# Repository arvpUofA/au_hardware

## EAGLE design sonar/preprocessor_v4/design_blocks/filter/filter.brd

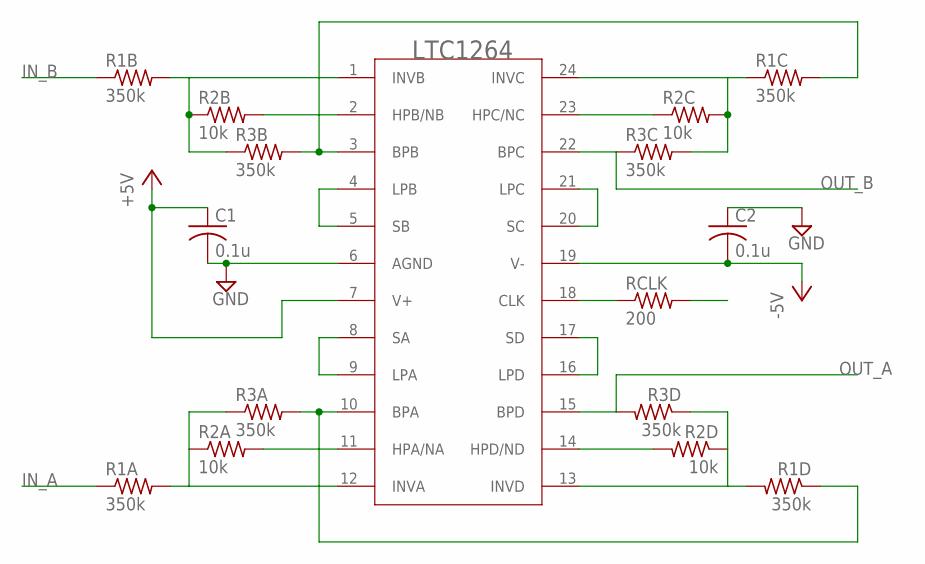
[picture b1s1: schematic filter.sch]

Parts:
C1, C2: 0.1u; C0805
R1A, R1B, R1C, R1D, R3A, R3B, R3C, R3D: 350k; R0805
R2A, R2B, R2C, R2D: 10k; R0805
RCLK: 200; R0805
U$1: LTC1264SMD; SO24W

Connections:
+5V: C1.1, U$1.7 (V+)
-5V: C2.2, U$1.19 (V-)
CLK: RCLK.2
GND: C1.2, C2.1, U$1.6 (AGND)
IN_A: R1A.1
IN_B: R1B.1
unnamed: R2D.2, U$1.14 (HPD/ND)
unnamed: R1D.2, R2D.1, R3D.1, U$1.13 (INVD)
unnamed: U$1.16 (LPD), U$1.17 (SD)
unnamed: R2C.1, U$1.23 (HPC/NC)
unnamed: R1C.1, R2C.2, R3C.2, U$1.24 (INVC)
unnamed: R2B.2, U$1.2 (HPB/NB)
unnamed: R1B.2, R2B.1, R3B.1, U$1.1 (INVB)
unnamed: U$1.4 (LPB), U$1.5 (SB)
unnamed: U$1.20 (SC), U$1.21 (LPC)
unnamed: RCLK.1, U$1.18 (CLK)
unnamed: R2A.2, U$1.11 (HPA/NA)
unnamed: U$1.8 (SA), U$1.9 (LPA)
unnamed: R1A.2, R2A.1, R3A.1, U$1.12 (INVA)
OUT_2ND_A: R1D.1, R3A.2, U$1.10 (BPA)
OUT_2ND_ORDER_B: R1C.2, R3B.2, U$1.3 (BPB)
OUT_A: R3D.2, U$1.15 (BPD)
OUT_B: R3C.1, U$1.22 (BPC)

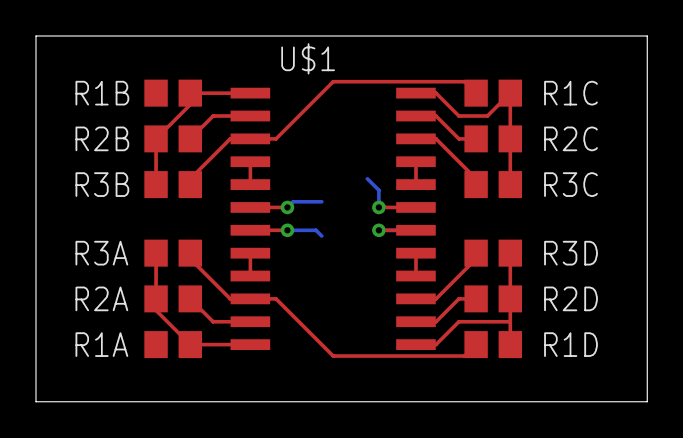
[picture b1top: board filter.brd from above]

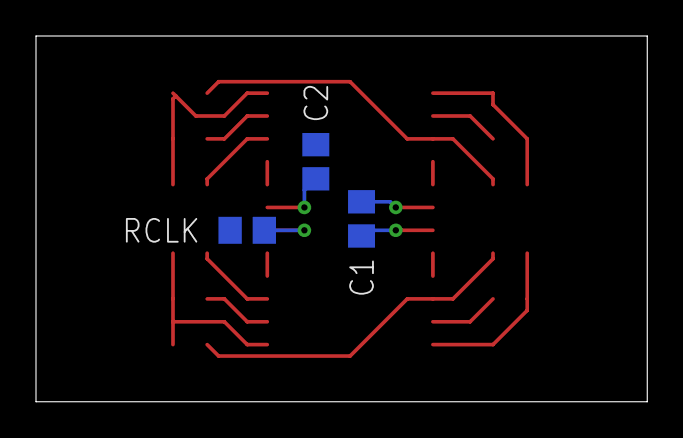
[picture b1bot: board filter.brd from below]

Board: 2 copper layers, 34.0 x 20.3 mm, 16 parts (3 on the bottom side), 20 nets.

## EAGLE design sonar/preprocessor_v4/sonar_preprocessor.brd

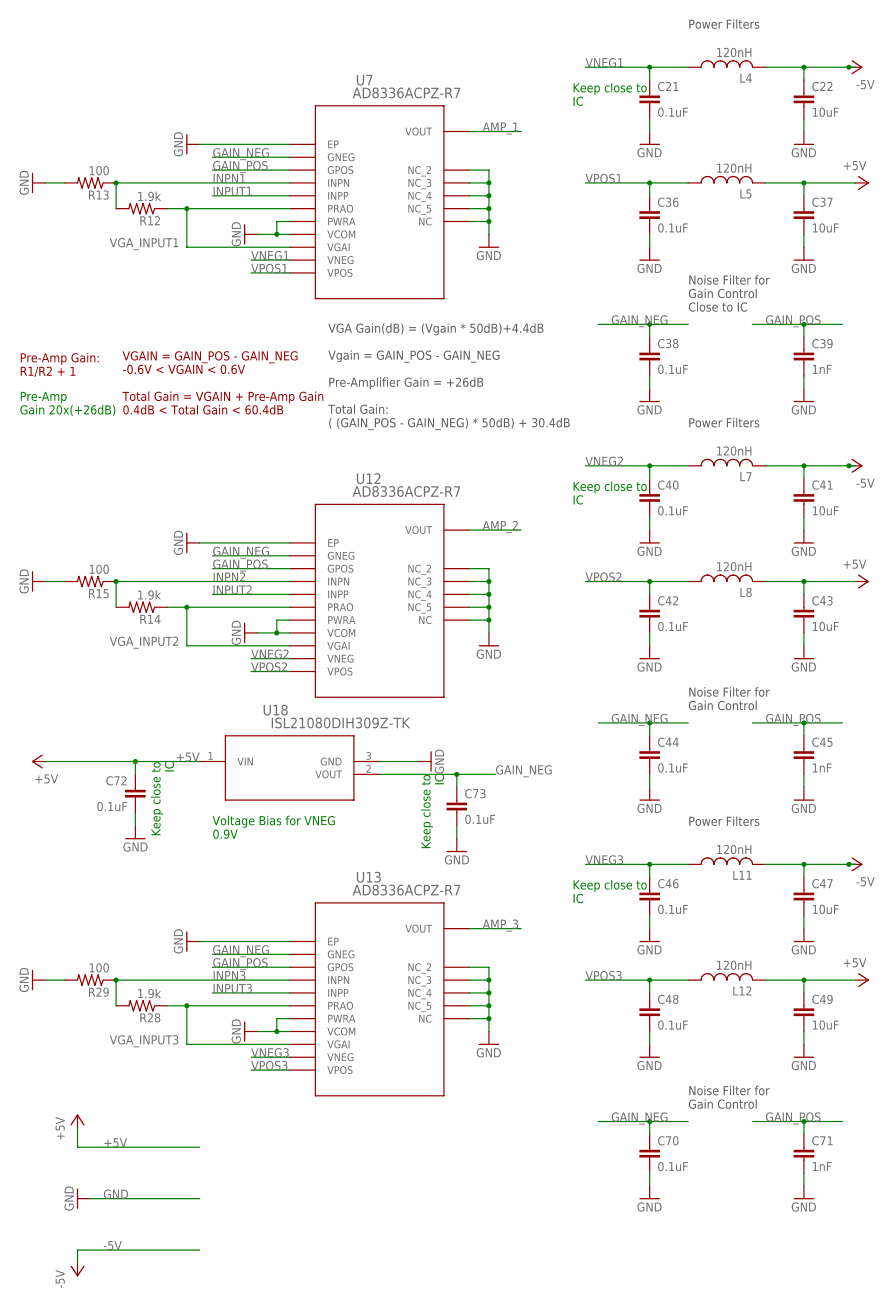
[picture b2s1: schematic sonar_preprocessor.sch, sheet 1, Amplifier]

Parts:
C21, C36, C38, C40, C42, C44, C46, C48, C70, C72, C73: 0.1uF; C0603
C22, C37, C41, C43, C47, C49: 10uF; C1206
C39, C45, C71: 1nF; C0603
L4, L5, L7, L8, L11, L12: 120nH; L3225P
R12, R14, R28: 1.9k; R0603
R13, R15, R29: 100; R0603
U7, U12, U13: AD8336ACPZ-R7; CP_16_4
U18: ISL21080DIH309Z-TK; P3_064

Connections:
+5V: C37.1, C43.1, C49.1, C72.1, L5.2, L8.2, L12.2, U18.1 (VIN); also elsewhere on the board
-5V: C22.1, C41.1, C47.1, L4.2, L7.2, L11.2; also elsewhere on the board
AMP_1: U7.VOUT; also elsewhere on the board
AMP_2: U12.VOUT; also elsewhere on the board
AMP_3: U13.VOUT; also elsewhere on the board
GAIN_NEG: C38.1, C44.1, C70.1, C73.1, U7.GNEG, U12.GNEG, U13.GNEG, U18.2 (VOUT)
GAIN_POS: C39.1, C45.1, C71.1, U7.GPOS, U12.GPOS, U13.GPOS; also elsewhere on the board
GND: C21.2, C22.2, C36.2, C37.2, C38.2, C39.2, C40.2, C41.2, C42.2, C43.2, C44.2, C45.2, C46.2, C47.2, C48.2, C49.2, C70.2, C71.2, C72.2, C73.2, R13.2, R15.2, R29.2, U7.GND1 (EP), U7.NC, U7.NC1 (NC_2), U7.NC2 (NC_3), U7.NC3 (NC_4), U7.NC4 (NC_5), U7.PWRA, U7.VCOM, U12.GND1 (EP), U12.NC, U12.NC1 (NC_2), U12.NC2 (NC_3), U12.NC3 (NC_4), U12.NC4 (NC_5), U12.PWRA, U12.VCOM, U13.GND1 (EP), U13.NC, U13.NC1 (NC_2), U13.NC2 (NC_3), U13.NC3 (NC_4), U13.NC4 (NC_5), U13.PWRA, U13.VCOM, U18.3 (GND); also elsewhere on the board
INPN1: R12.2, R13.1, U7.INPN
INPN2: R14.2, R15.1, U12.INPN
INPN3: R28.2, R29.1, U13.INPN
INPUT1: U7.INPP; also elsewhere on the board
INPUT2: U12.INPP; also elsewhere on the board
INPUT3: U13.INPP; also elsewhere on the board
VGA_INPUT1: R12.1, U7.PRAO, U7.VGAI
VGA_INPUT2: R14.1, U12.PRAO, U12.VGAI
VGA_INPUT3: R28.1, U13.PRAO, U13.VGAI
VNEG1: C21.1, L4.1, U7.VNEG
VNEG2: C40.1, L7.1, U12.VNEG
VNEG3: C46.1, L11.1, U13.VNEG
VPOS1: C36.1, L5.1, U7.VPOS
VPOS2: C42.1, L8.1, U12.VPOS
VPOS3: C48.1, L12.1, U13.VPOS

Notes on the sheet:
Pre-Amp Gain 20x(+26dB)
Power Filters
Keep close to IC
Noise Filter for Gain Control Close to IC
Pre-Amp Gain: R1/R2 + 1
VGA Gain(dB) = (Vgain * 50dB)+4.4dB Vgain = GAIN_POS - GAIN_NEG Pre-Amplifier Gain = +26dB Total Gain: ( (GAIN_POS - GAIN_NEG) * 50dB) + 30.4dB
VGAIN = GAIN_POS - GAIN_NEG -0.6V < VGAIN < 0.6V Total Gain = VGAIN + Pre-Amp Gain 0.4dB < Total Gain < 60.4dB
Noise Filter for Gain Control
Voltage Bias for VNEG 0.9V

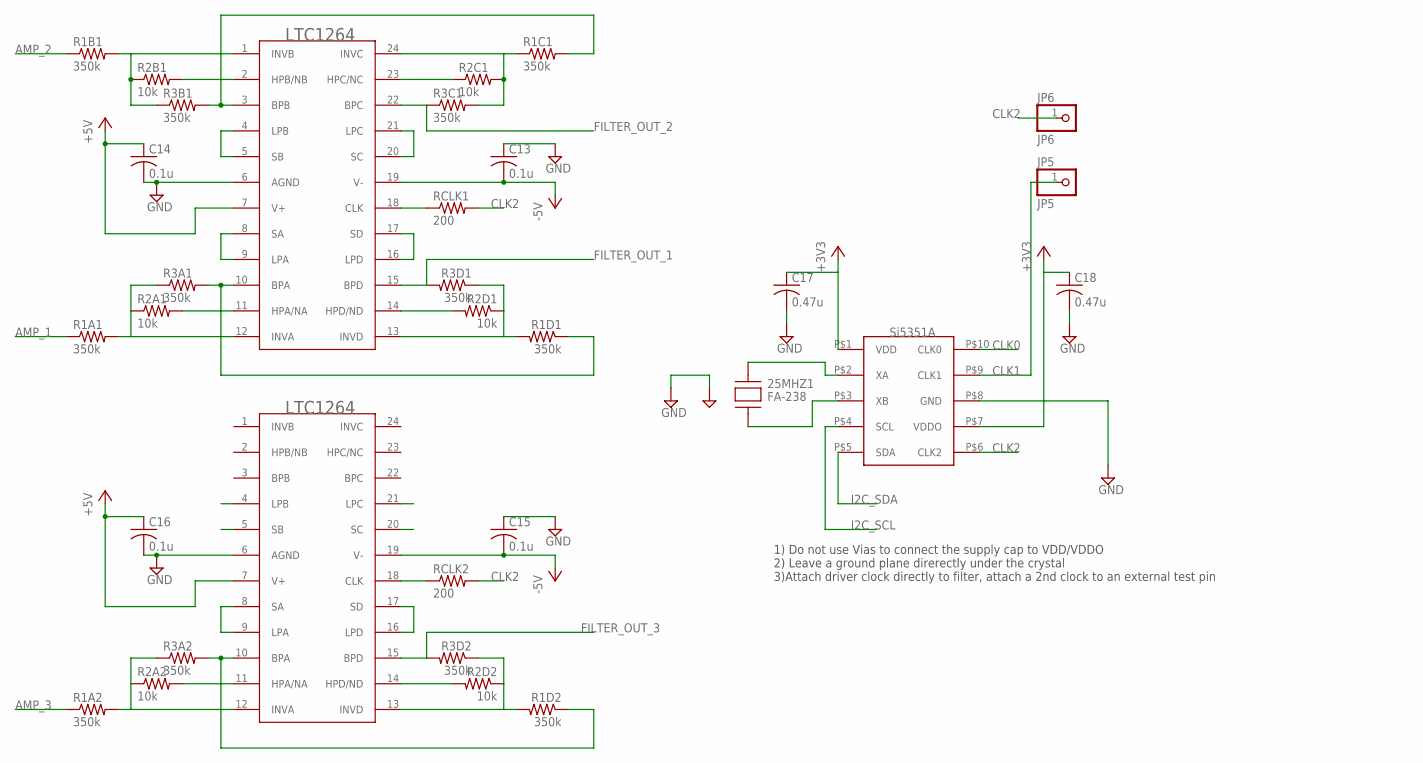
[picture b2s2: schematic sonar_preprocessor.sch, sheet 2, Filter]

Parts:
25MHZ1: FA-238
C13, C14, C15, C16: 0.1u; C0805
C17, C18: 0.47u; C0805
JP5: JP5; 1X01
JP6: JP6; 1X01
R1A1, R1A2, R1B1, R1C1, R1D1, R1D2, R3A1, R3A2, R3B1, R3C1, R3D1, R3D2: 350k; R0805
R2A1, R2A2, R2B1, R2C1, R2D1, R2D2: 10k; R0805
RCLK1, RCLK2: 200; R0805
U$6, U$7: LTC1264SMD; SO24W
U$8: SI5351A; MSOP-10

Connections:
+3V3: C17.1, C18.1, U$8.P$1 (VDD), U$8.P$7 (VDDO); also elsewhere on the board
+5V: C14.1, C16.1, U$6.7 (V+), U$7.7 (V+); also elsewhere on the board
-5V: C13.2, C15.2, U$6.19 (V-), U$7.19 (V-); also elsewhere on the board
AMP_1: R1A1.1; also elsewhere on the board
AMP_2: R1B1.1; also elsewhere on the board
AMP_3: R1A2.1; also elsewhere on the board
CLK0: U$8.P$10 (CLK0)
CLK1: JP5.1, U$8.P$9 (CLK1)
CLK2: JP6.1, RCLK1.2, RCLK2.2, U$8.P$6 (CLK2)
FILTER_OUT_1: R3D1.2, U$6.15 (BPD); also elsewhere on the board
FILTER_OUT_2: R3C1.1, U$6.22 (BPC); also elsewhere on the board
FILTER_OUT_3: R3D2.2, U$7.15 (BPD); also elsewhere on the board
GND: 25MHZ1.P$1 (GND), 25MHZ1.P$3 (GND), C13.1, C14.2, C15.1, C16.2, C17.2, C18.2, U$6.6 (AGND), U$7.6 (AGND), U$8.P$8 (GND); also elsewhere on the board
I2C_SCL: U$8.P$4 (SCL); also elsewhere on the board
I2C_SDA: U$8.P$5 (SDA); also elsewhere on the board
unnamed: 25MHZ1.P$4 (XA), U$8.P$2 (XA)
unnamed: 25MHZ1.P$2 (XB), U$8.P$3 (XB)
unnamed: R2A1.2, U$6.11 (HPA/NA)
unnamed: U$6.8 (SA), U$6.9 (LPA)
unnamed: R1A1.2, R2A1.1, R3A1.1, U$6.12 (INVA)
unnamed: R2D1.2, U$6.14 (HPD/ND)
unnamed: R1D1.2, R2D1.1, R3D1.1, U$6.13 (INVD)
unnamed: U$6.16 (LPD), U$6.17 (SD)
unnamed: R2C1.1, U$6.23 (HPC/NC)
unnamed: R1C1.1, R2C1.2, R3C1.2, U$6.24 (INVC)
unnamed: R2B1.2, U$6.2 (HPB/NB)
unnamed: R1B1.2, R2B1.1, R3B1.1, U$6.1 (INVB)
unnamed: U$6.4 (LPB), U$6.5 (SB)
unnamed: U$6.20 (SC), U$6.21 (LPC)
unnamed: RCLK1.1, U$6.18 (CLK)
unnamed: R2A2.2, U$7.11 (HPA/NA)
unnamed: U$7.8 (SA), U$7.9 (LPA)
unnamed: R1A2.2, R2A2.1, R3A2.1, U$7.12 (INVA)
unnamed: R2D2.2, U$7.14 (HPD/ND)
unnamed: R1D2.2, R2D2.1, R3D2.1, U$7.13 (INVD)
unnamed: U$7.16 (LPD), U$7.17 (SD)
unnamed: RCLK2.1, U$7.18 (CLK)
OUT_2ND_A1: R1D1.1, R3A1.2, U$6.10 (BPA)
OUT_2ND_A2: R1D2.1, R3A2.2, U$7.10 (BPA)
OUT_2ND_ORDER_B1: R1C1.2, R3B1.2, U$6.3 (BPB)

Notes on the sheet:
1) Do not use Vias to connect the supply cap to VDD/VDDO 2) Leave a ground plane direrectly under the crystal 3)Attach driver clock directly to filter, attach a 2nd clock to an external test pin

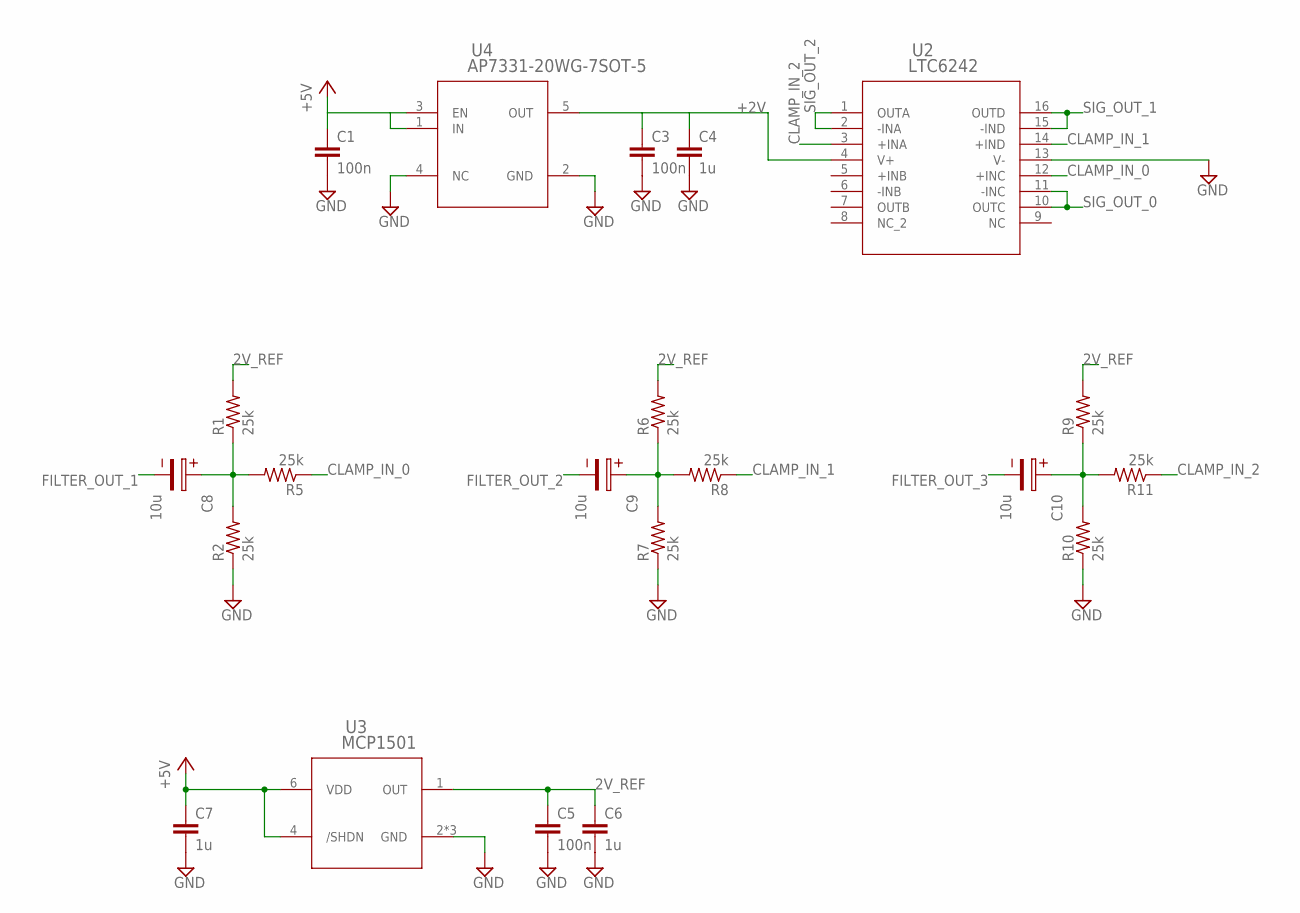
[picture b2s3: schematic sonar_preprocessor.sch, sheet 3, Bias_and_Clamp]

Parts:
C1, C3, C5: 100n; C0805
C4, C6, C7: 1u; C0805
C8, C9, C10: 10u; 2.6X1.6X1(BXCXA)
R1, R2, R5, R6, R7, R8, R9, R10, R11: 25k; R0805
U2: LTC6242; SSOP16
U3: MCP1501; SOT23-6
U4: AP7331-20WG-7SOT-5; SOT23-5

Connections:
2V_REF: C5.1, C6.1, R1.2, R6.2, R9.2, U3.1 (OUT)
+2V: C3.1, C4.1, U2.4 (V+), U4.5 (OUT)
+5V: C1.1, C7.1, U3.4 (/SHDN), U3.6 (VDD), U4.1 (IN), U4.3 (EN); also elsewhere on the board
BIASED_0: C8.1, R1.1, R2.2, R5.2
BIASED_1: C9.1, R6.1, R7.2, R8.2
BIASED_2: C10.1, R9.1, R10.2, R11.2
CLAMP_IN_0: R5.1, U2.12 (+INC)
CLAMP_IN_1: R8.1, U2.14 (+IND)
CLAMP_IN_2: R11.1, U2.3 (+INA)
FILTER_OUT_1: C8.2; also elsewhere on the board
FILTER_OUT_2: C9.2; also elsewhere on the board
FILTER_OUT_3: C10.2; also elsewhere on the board
GND: C1.2, C3.2, C4.2, C5.2, C6.2, C7.2, R2.1, R7.1, R10.1, U2.13 (V-), U3.2 (GND), U3.3 (GND), U3.5 (GND), U4.2 (GND), U4.4 (NC); also elsewhere on the board
SIG_OUT_0: U2.10 (OUTC), U2.11 (-INC); also elsewhere on the board
SIG_OUT_1: U2.15 (-IND), U2.16 (OUTD); also elsewhere on the board
SIG_OUT_2: U2.1 (OUTA), U2.2 (-INA); also elsewhere on the board

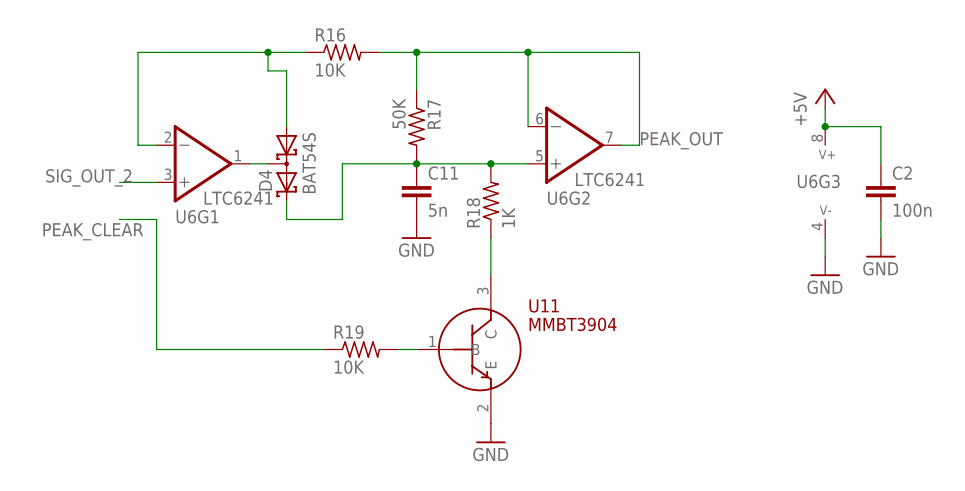
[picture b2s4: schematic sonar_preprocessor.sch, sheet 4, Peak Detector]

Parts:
C2: 100n; C0805
C11: 5n; C0805
D4: BAT54S; SOT23
R16, R19: 10K; R0805
R17: 50K; R0805
R18: 1K; R0805
U6: LTC6241; SO-8
U11: MMBT3904; SOT23

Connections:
+5V: C2.1, U6.8 (V+); also elsewhere on the board
GND: C2.2, C11.2, U6.4 (V-), U11.2 (E); also elsewhere on the board
unnamed: C11.1, D4.2 (C2), R17.2, R18.2, U6.5 (+IN)
unnamed: D4.1 (A1), R16.1, U6.2 (-IN)
unnamed: D4.3 (C1A2), U6.1 (OUT)
unnamed: R19.2, U11.1 (B)
unnamed: R18.1, U11.3 (C)
PEAK_CLEAR: R19.1; also elsewhere on the board
PEAK_OUT: R16.2, R17.1, U6.6 (-IN), U6.7 (OUT); also elsewhere on the board
SIG_OUT_2: U6.3 (+IN); also elsewhere on the board

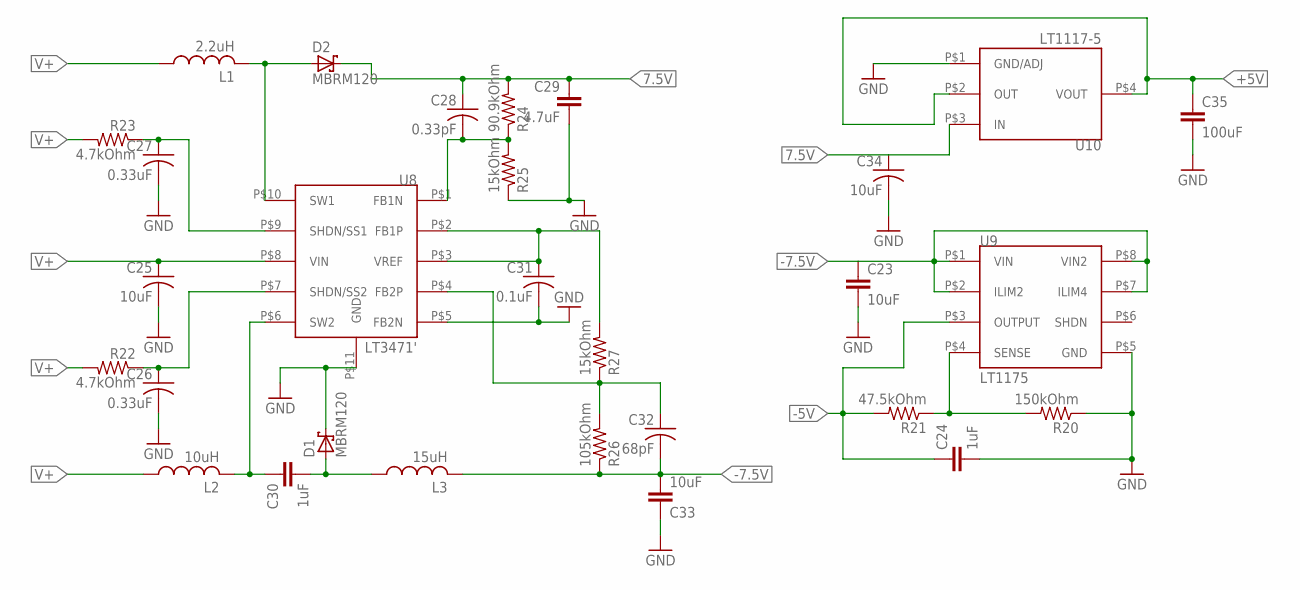
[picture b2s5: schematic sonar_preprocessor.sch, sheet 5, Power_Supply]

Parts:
C23, C33: 10uF; C0805
C24, C30: 1uF; C1206
C25, C34: 10uF; C0603
C26, C27: 0.33uF; C0603
C28: 0.33pF; C0603
C29: 4.7uF; C1206
C31: 0.1uF; C0603
C32: 68pF; C0603
C35: 100uF; C1210
D1, D2: MBRM120; DO-216AA
L1: 2.2uH; NS4.9X4.9
L2: 10uH; NS5X5
L3: 15uH; NS5X5
R20: 150kOhm; R0603
R21: 47.5kOhm; R0603
R22, R23: 4.7kOhm; R0603
R24: 90.9kOhm; R0603
R25, R27: 15kOhm; R0603
R26: 105kOhm; R0603
U8: LT3471'; 10-WFDFN
U9: LT1175; 8-SOIC
U10: LT1117-5; SOT233-3

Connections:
7.5V: C28.1, C29.1, C34.1, D2.P$1 (C), R24.2, U10.P$3 (IN)
+5V: C35.1, U10.P$2 (OUT), U10.P$4 (VOUT); also elsewhere on the board
-5V: C24.1, R21.2, U9.P$3 (OUTPUT); also elsewhere on the board
-7.5V: C23.1, C32.2, C33.2, L3.P$2 (2), R26.1, U9.P$1 (VIN), U9.P$2 (ILIM2), U9.P$7 (ILIM4), U9.P$8 (VIN2)
GND: C23.2, C24.2, C25.2, C26.2, C27.2, C29.2, C31.2, C33.1, C34.2, C35.2, D1.P$1 (C), R20.1, R25.1, U8.P$5 (FB2N), U8.P$11 (GND), U9.P$5 (GND), U10.P$1 (GND/ADJ); also elsewhere on the board
unnamed: R20.2, R21.1, U9.P$4 (SENSE)
unnamed: D2.P$2 (A), L1.P$2 (2), U8.P$10 (SW1)
unnamed: C28.2, R24.1, R25.2, U8.P$1 (FB1N)
unnamed: C30.1, L2.P$2 (2), U8.P$6 (SW2)
unnamed: C30.2, D1.P$2 (A), L3.P$1 (1)
unnamed: C32.1, R26.2, R27.1, U8.P$4 (FB2P)
SS3: C26.1, R22.1, U8.P$7 (SHDN/SS2)
SS4: C27.1, R23.1, U8.P$9 (SHDN/SS1)
V+: C25.1, L1.P$1 (1), L2.P$1 (1), R22.2, R23.2, U8.P$8 (VIN); also elsewhere on the board
VREF: C31.1, R27.2, U8.P$2 (FB1P), U8.P$3 (VREF)

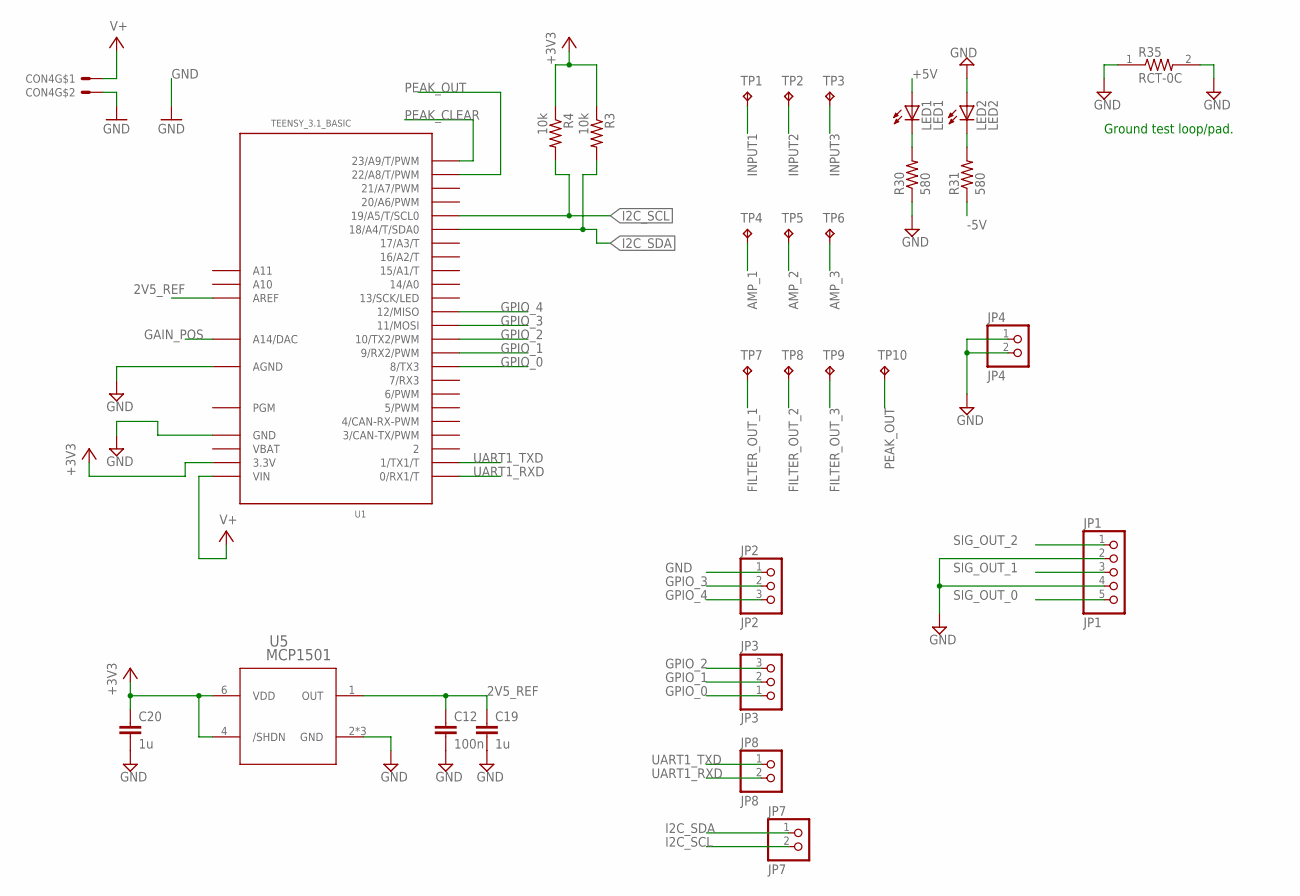
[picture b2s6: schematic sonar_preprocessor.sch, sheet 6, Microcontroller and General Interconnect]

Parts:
C12: 100n; C0805
C19, C20: 1u; C0805
CON4: MOLEX_5566-2; 5566-2
JP1: JP1; 1X05/90
JP2: JP2; 1X03SMD/90
JP3: JP3; 1X03SMD/90
JP4: JP4; 1X02
JP7: JP7; 1X02
JP8: JP8; 1X02SMD/90
LED1: LED1; SML0805
LED2: LED2; SML0805
R3, R4: 10k; R0805
R30, R31: 580; R0805
R35: RCT-0C; RESC2012X65N
TP1, TP2, TP3, TP4, TP5, TP6, TP7, TP8, TP9, TP10: TPB2,54; B2,54
U1: TEENSY_3.1_BASIC
U5: MCP1501; SOT23-6

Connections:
2V5_REF: C12.1, C19.1, U1.AREF, U5.1 (OUT)
+3V3: C20.1, R3.1, R4.1, U1.3.3V, U1.3.3V1 (3.3V), U5.4 (/SHDN), U5.6 (VDD); also elsewhere on the board
+5V: LED1.A; also elsewhere on the board
-5V: R31.1; also elsewhere on the board
AMP_1: TP4.TP; also elsewhere on the board
AMP_2: TP5.TP; also elsewhere on the board
AMP_3: TP6.TP; also elsewhere on the board
FILTER_OUT_1: TP7.TP; also elsewhere on the board
FILTER_OUT_2: TP8.TP; also elsewhere on the board
FILTER_OUT_3: TP9.TP; also elsewhere on the board
GAIN_POS: U1.A14 (A14/DAC); also elsewhere on the board
GND: C12.2, C19.2, C20.2, CON4.2, JP1.2, JP1.4, JP2.1, JP4.1, JP4.2, LED2.A, R30.1, R35.1, R35.2, U1.AGND, U1.GND, U1.GND1 (GND), U5.2 (GND), U5.3 (GND), U5.5 (GND); also elsewhere on the board
GPIO_0: JP3.1, U1.8 (8/TX3)
GPIO_1: JP3.2, U1.9 (9/RX2/PWM)
GPIO_2: JP3.3, U1.10 (10/TX2/PWM)
GPIO_3: JP2.2, U1.11 (11/MOSI)
GPIO_4: JP2.3, U1.12 (12/MISO)
I2C_SCL: JP7.2, R4.2, U1.19/A5 (19/A5/T/SCL0); also elsewhere on the board
I2C_SDA: JP7.1, R3.2, U1.18/A4 (18/A4/T/SDA0); also elsewhere on the board
INPUT1: TP1.TP; also elsewhere on the board
INPUT2: TP2.TP; also elsewhere on the board
INPUT3: TP3.TP; also elsewhere on the board
unnamed: LED2.C, R31.2
unnamed: LED1.C, R30.2
PEAK_CLEAR: U1.23/A9 (23/A9/T/PWM); also elsewhere on the board
PEAK_OUT: TP10.TP, U1.22/A8 (22/A8/T/PWM); also elsewhere on the board
SIG_OUT_0: JP1.5; also elsewhere on the board
SIG_OUT_1: JP1.3; also elsewhere on the board
SIG_OUT_2: JP1.1; also elsewhere on the board
UART1_RXD: JP8.2, U1.0 (0/RX1/T)
UART1_TXD: JP8.1, U1.1 (1/TX1/T)
V+: CON4.1, U1.VIN; also elsewhere on the board
VBAT: U1.VBAT

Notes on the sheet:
Ground test loop/pad.

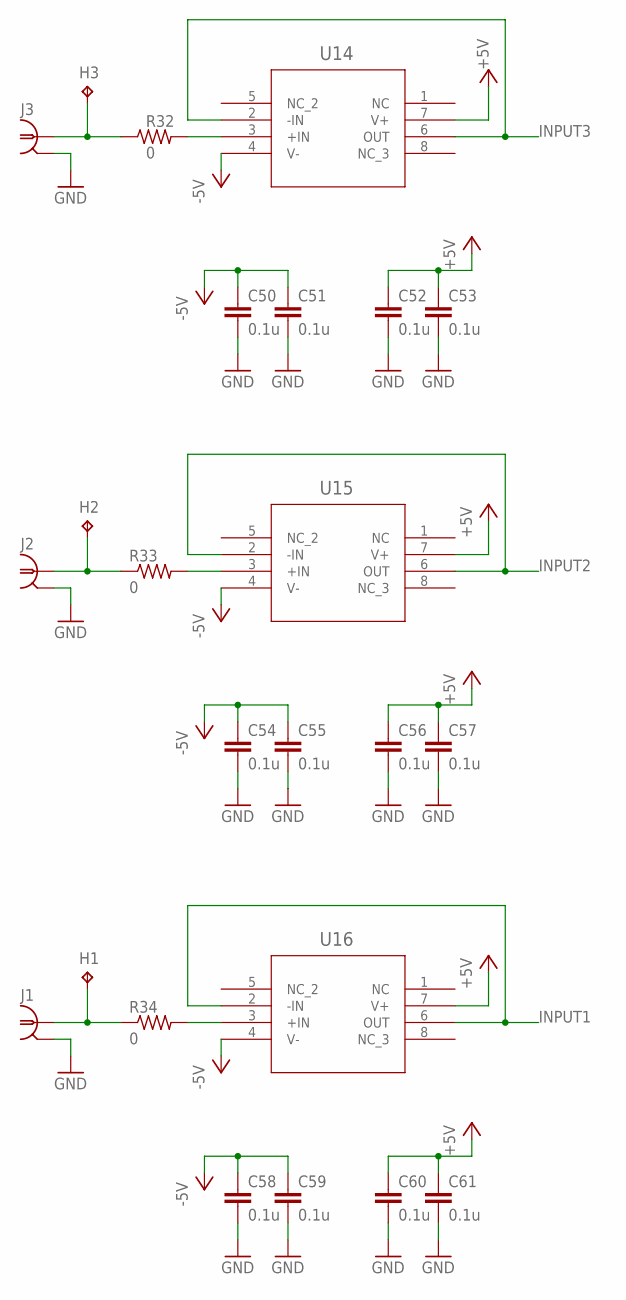
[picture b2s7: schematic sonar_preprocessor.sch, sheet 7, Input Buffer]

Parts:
C50, C51, C52, C53, C54, C55, C56, C57, C58, C59, C60, C61: 0.1u; C0603
H1, H2, H3: TPB2,54; B2,54
J1, J2, J3: TE_5-1634503-1TE; TE_5-1634503-1
R32, R33, R34: 0; R0603
U14: U14; SO-8
U15: U15; SO-8
U16: U16; SO-8

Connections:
+5V: C52.1, C53.1, C56.1, C57.1, C60.1, C61.1, U14.7 (V+), U15.7 (V+), U16.7 (V+); also elsewhere on the board
-5V: C50.1, C51.1, C54.1, C55.1, C58.1, C59.1, U14.4 (V-), U15.4 (V-), U16.4 (V-); also elsewhere on the board
GND: C50.2, C51.2, C52.2, C53.2, C54.2, C55.2, C56.2, C57.2, C58.2, C59.2, C60.2, C61.2, J1.2, J1.3 (2), J1.4 (2), J1.5 (2), J2.2, J2.3 (2), J2.4 (2), J2.5 (2), J3.2, J3.3 (2), J3.4 (2), J3.5 (2); also elsewhere on the board
INPUT1: U16.2 (-IN), U16.6 (OUT); also elsewhere on the board
INPUT2: U15.2 (-IN), U15.6 (OUT); also elsewhere on the board
INPUT3: U14.2 (-IN), U14.6 (OUT); also elsewhere on the board
unnamed: H3.TP, J3.1, R32.1
unnamed: R32.2, U14.3 (+IN)
unnamed: H2.TP, J2.1, R33.1
unnamed: R33.2, U15.3 (+IN)
unnamed: R34.2, U16.3 (+IN)
unnamed: H1.TP, J1.1, R34.1

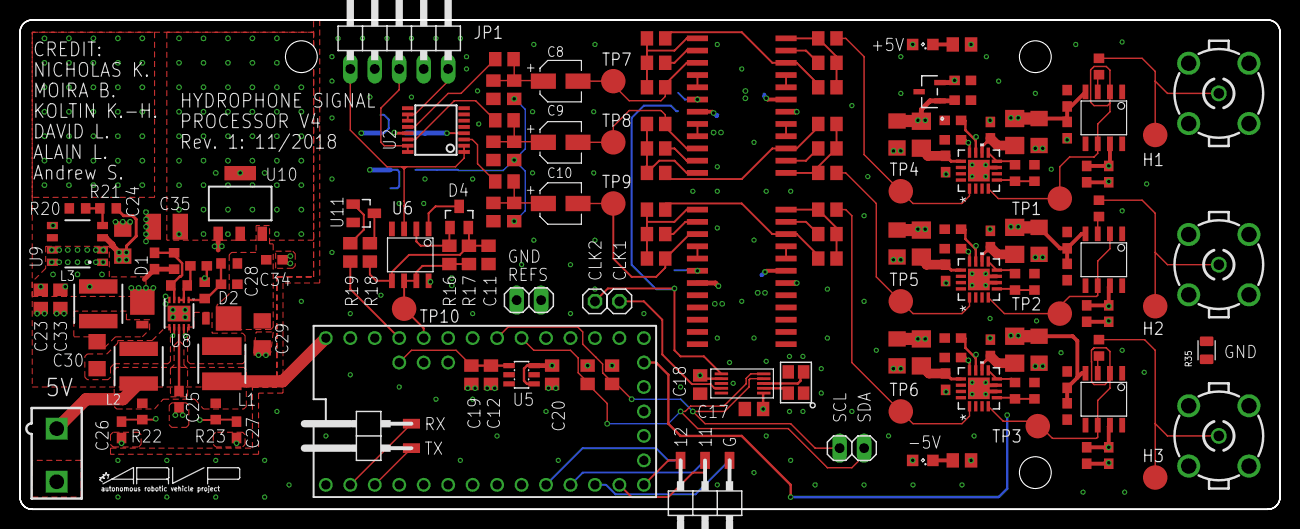
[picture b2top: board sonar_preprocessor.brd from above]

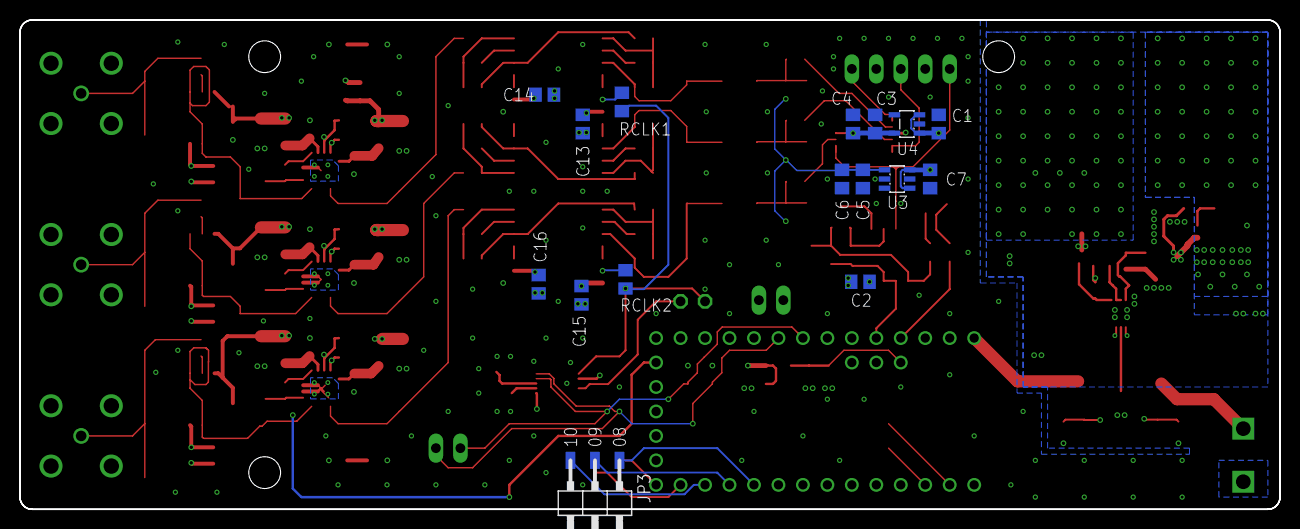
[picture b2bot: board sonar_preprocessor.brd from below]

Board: 4 copper layers, 130.8 x 50.8 mm, 185 parts (16 on the bottom side), 102 nets.

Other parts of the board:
U$1: A4L-LOC
U$2, U$3, U$5: STAND-OFF
U$4: ARVP

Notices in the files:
parts and their libraries:
Kondensatoren: Copyright: Würth Elektronik
